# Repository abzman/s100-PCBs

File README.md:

# s100-PCBs
replica PCBs including backplanes and interface cards

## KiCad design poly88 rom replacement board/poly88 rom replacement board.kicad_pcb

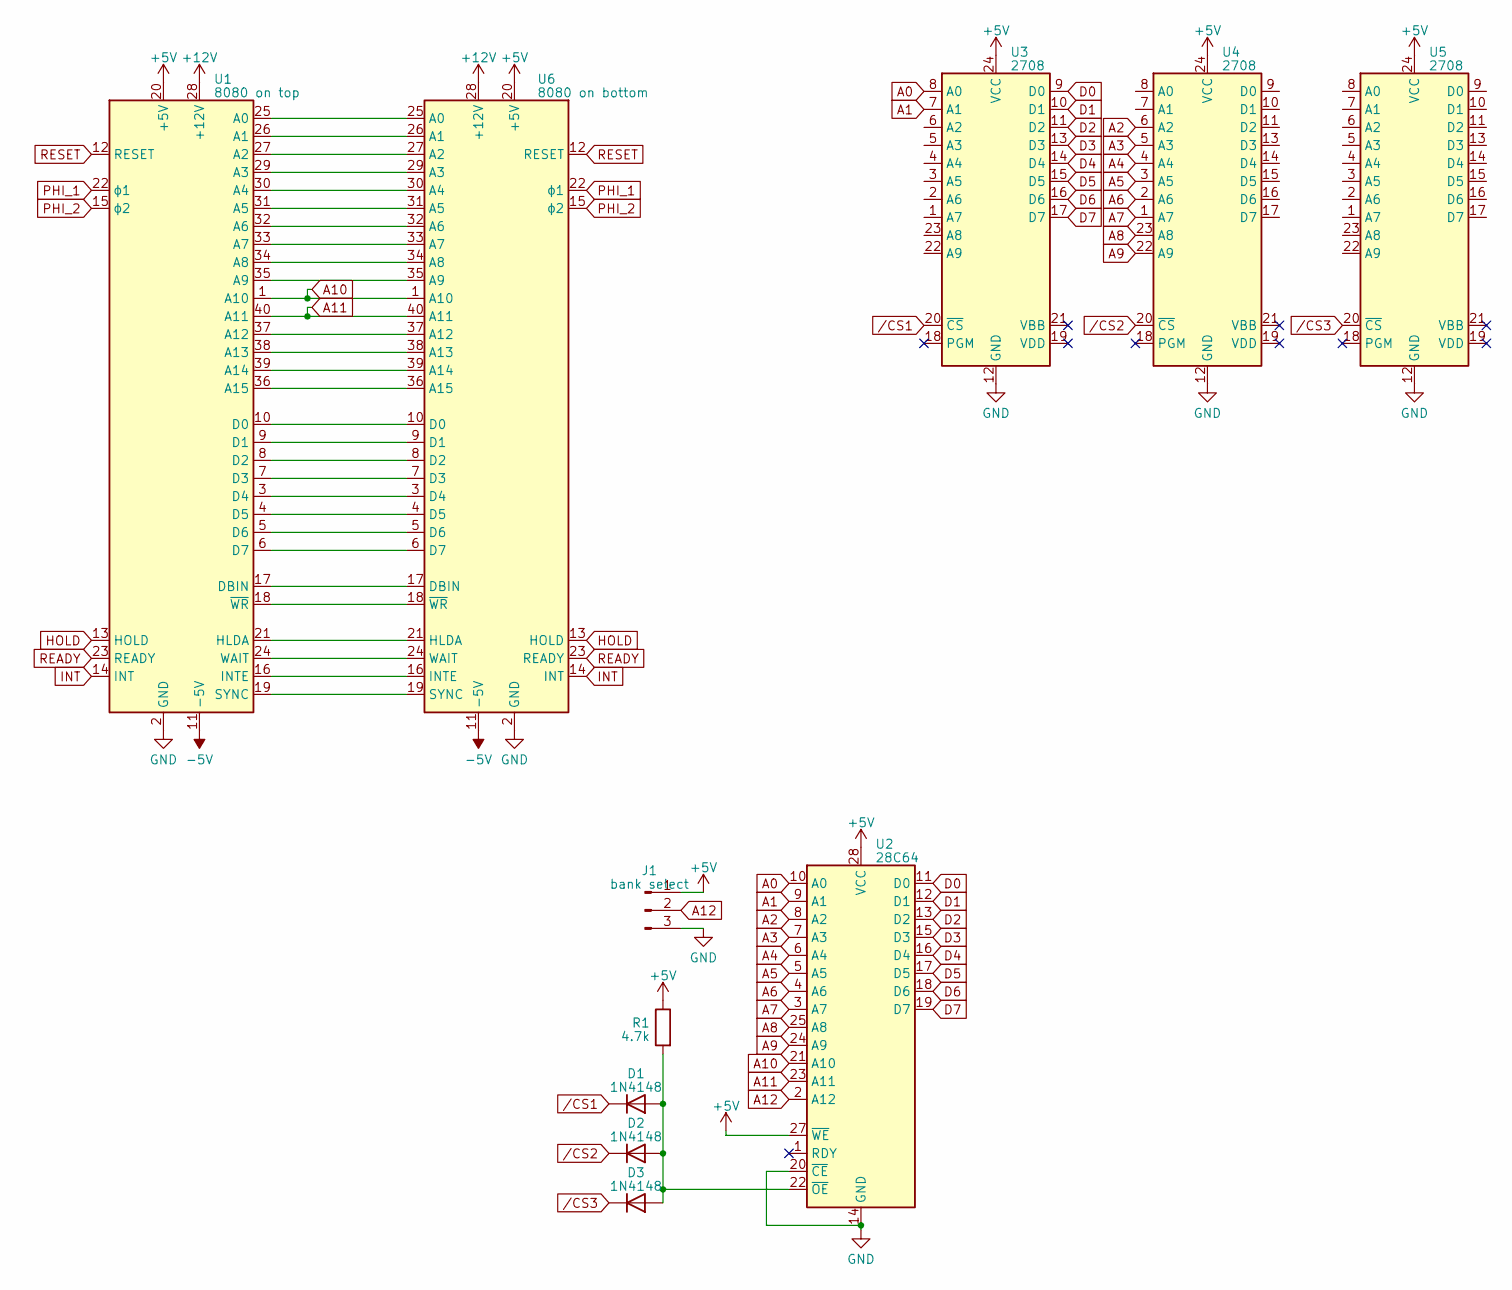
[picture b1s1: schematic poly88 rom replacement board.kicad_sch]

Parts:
D1, D2, D3: 1N4148; D_DO-35_SOD27_P7.62mm_Horizontal
J1: bank select; PinHeader_1x03_P2.54mm_Vertical
R1: 4.7k; R_Axial_DIN0207_L6.3mm_D2.5mm_P7.62mm_Horizontal
U1: 8080 on top; DIP-40_W15.24mm
U2: 28C64; DIP-28_W15.24mm
U3, U4, U5: 2708; DIP-24_W15.24mm
U6: 8080 on bottom; DIP-40_W15.24mm

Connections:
+5V: J1.1, R1.1, U1.20 (+5V), U2.27 (~WE), U2.28 (VCC), U3.24 (VCC), U4.24 (VCC), U5.24 (VCC), U6.20 (+5V)
+12V: U1.28 (+12V), U6.28 (+12V)
-5V: U1.11 (-5V), U6.11 (-5V)
A0: U2.10 (A0), U3.8 (A0)
A1: U2.9 (A1), U3.7 (A1)
A2: U2.8 (A2), U4.6 (A2)
A3: U2.7 (A3), U4.5 (A3)
A4: U2.6 (A4), U4.4 (A4)
A5: U2.5 (A5), U4.3 (A5)
A6: U2.4 (A6), U4.2 (A6)
A7: U2.3 (A7), U4.1 (A7)
A8: U2.25 (A8), U4.23 (A8)
A9: U2.24 (A9), U4.22 (A9)
A10: U1.1 (A10), U2.21 (A10), U6.1 (A10)
A11: U1.40 (A11), U2.23 (A11), U6.40 (A11)
A12: J1.2, U2.2 (A12)
D0: U2.11 (D0), U3.9 (D0)
D1: U2.12 (D1), U3.10 (D1)
D2: U2.13 (D2), U3.11 (D2)
D3: U2.15 (D3), U3.13 (D3)
D4: U2.16 (D4), U3.14 (D4)
D5: U2.17 (D5), U3.15 (D5)
D6: U2.18 (D6), U3.16 (D6)
D7: U2.19 (D7), U3.17 (D7)
GND: J1.3, U1.2 (GND), U2.14 (GND), U2.20 (~CE), U3.12 (GND), U4.12 (GND), U5.12 (GND), U6.2 (GND)
HOLD: U1.13 (HOLD), U6.13 (HOLD)
INT: U1.14 (INT), U6.14 (INT)
unnamed: D1.2 (A), D2.2 (A), D3.2 (A), R1.2, U2.22 (~OE)
unnamed: U1.25 (A0), U6.25 (A0)
unnamed: U1.26 (A1), U6.26 (A1)
unnamed: U1.27 (A2), U6.27 (A2)
unnamed: U1.29 (A3), U6.29 (A3)
unnamed: U1.30 (A4), U6.30 (A4)
unnamed: U1.31 (A5), U6.31 (A5)
unnamed: U1.32 (A6), U6.32 (A6)
unnamed: U1.33 (A7), U6.33 (A7)
unnamed: U1.34 (A8), U6.34 (A8)
unnamed: U1.35 (A9), U6.35 (A9)
unnamed: U1.37 (A12), U6.37 (A12)
unnamed: U1.38 (A13), U6.38 (A13)
unnamed: U1.39 (A14), U6.39 (A14)
unnamed: U1.36 (A15), U6.36 (A15)
unnamed: U1.10 (D0), U6.10 (D0)
unnamed: U1.9 (D1), U6.9 (D1)
unnamed: U1.8 (D2), U6.8 (D2)
unnamed: U1.7 (D3), U6.7 (D3)
unnamed: U1.3 (D4), U6.3 (D4)
unnamed: U1.4 (D5), U6.4 (D5)
unnamed: U1.5 (D6), U6.5 (D6)
unnamed: U1.6 (D7), U6.6 (D7)
unnamed: U1.17 (DBIN), U6.17 (DBIN)
unnamed: U1.21 (HLDA), U6.21 (HLDA)
unnamed: U1.16 (INTE), U6.16 (INTE)
unnamed: U1.19 (SYNC), U6.19 (SYNC)
unnamed: U1.24 (WAIT), U6.24 (WAIT)
unnamed: U1.18 (~WR), U6.18 (~WR)
PHI_1: U1.22 (ϕ1), U6.22 (ϕ1)
PHI_2: U1.15 (ϕ2), U6.15 (ϕ2)
READY: U1.23 (READY), U6.23 (READY)
RESET: U1.12 (RESET), U6.12 (RESET)
/CS1: D1.1 (K), U3.20 (~CS)
/CS2: D2.1 (K), U4.20 (~CS)
/CS3: D3.1 (K), U5.20 (~CS)

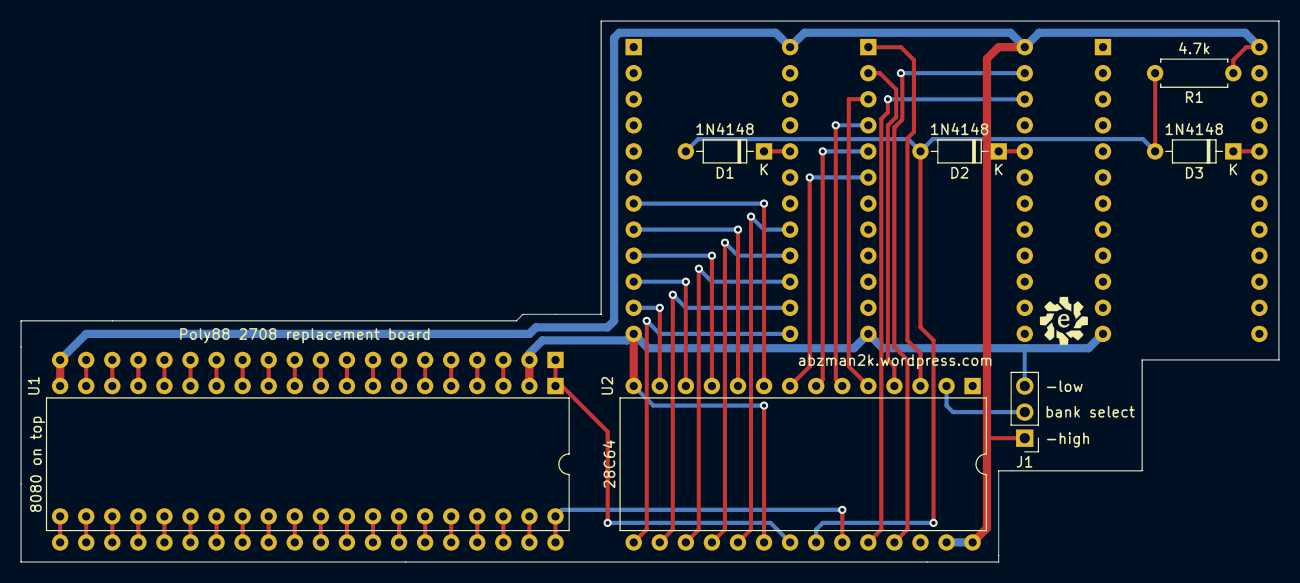
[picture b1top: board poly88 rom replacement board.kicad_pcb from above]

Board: 2 copper layers, 122.6 x 52.7 mm, 11 parts (0 on the bottom side), 63 nets.

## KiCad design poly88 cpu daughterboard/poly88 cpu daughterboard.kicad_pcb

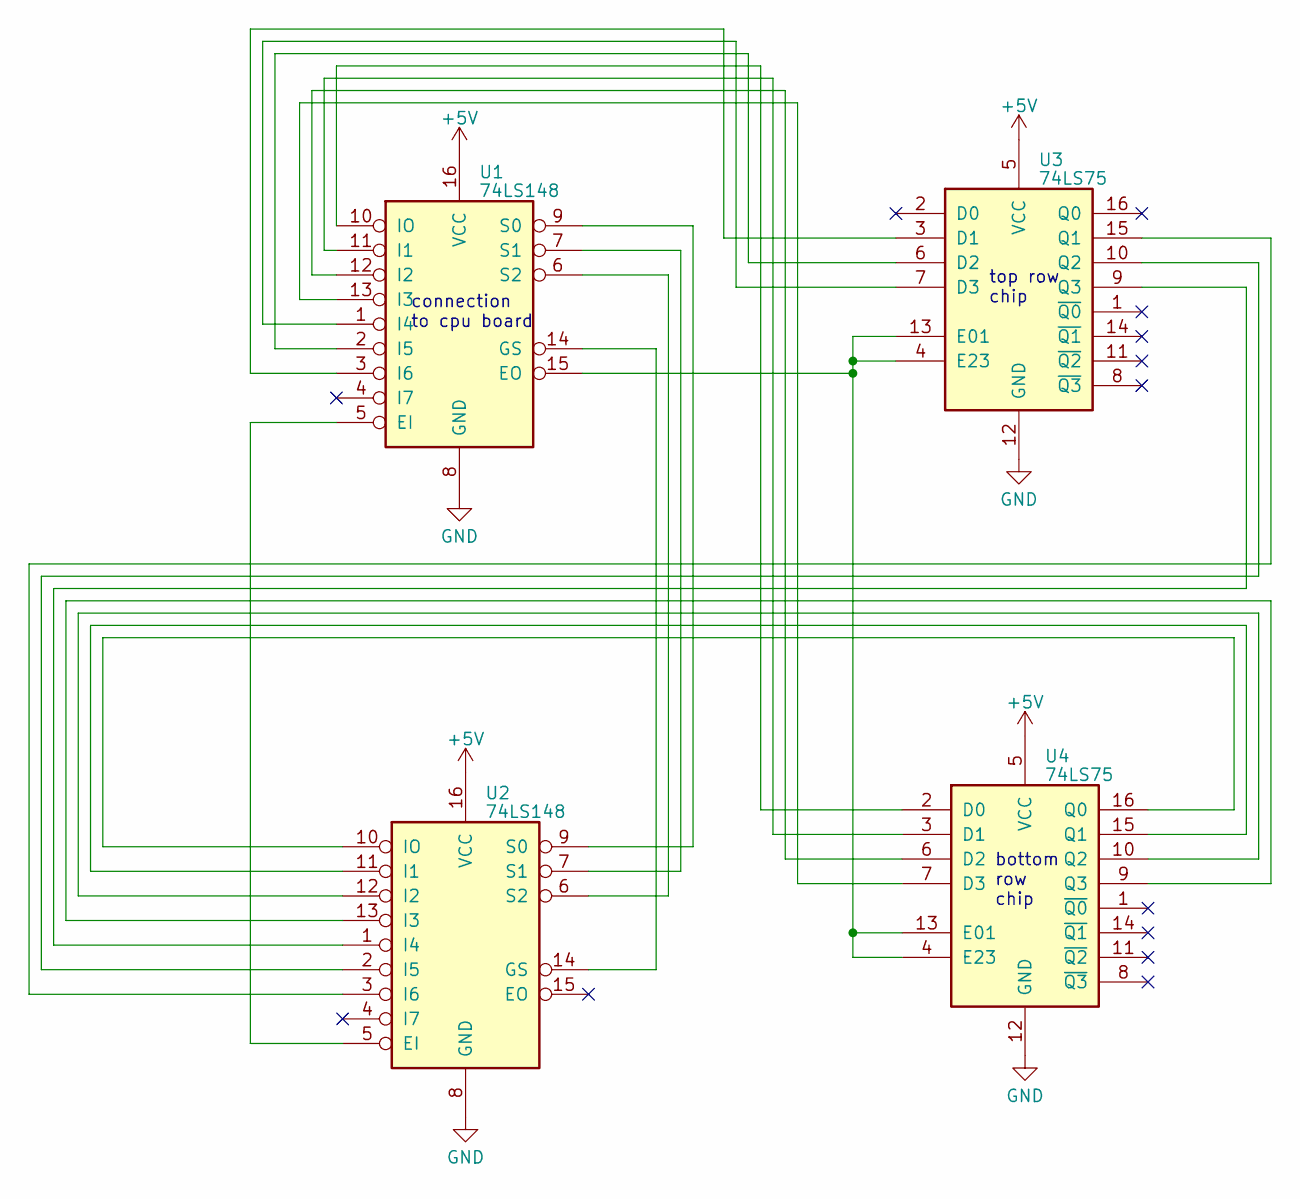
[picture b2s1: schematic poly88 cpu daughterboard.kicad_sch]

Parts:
U1, U2: 74LS148; DIP-16_W7.62mm
U3, U4: 74LS75; DIP-16_W7.62mm

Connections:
+5V: U1.16 (VCC), U2.16 (VCC), U3.5 (VCC), U4.5 (VCC)
GND: U1.8 (GND), U2.8 (GND), U3.12 (GND), U4.12 (GND)
unnamed: U1.5 (EI), U2.5 (EI)
unnamed: U1.15 (EO), U3.4 (E23), U3.13 (E01), U4.4 (E23), U4.13 (E01)
unnamed: U1.14 (GS), U2.14 (GS)
unnamed: U1.11 (I1), U4.3 (D1)
unnamed: U1.12 (I2), U4.6 (D2)
unnamed: U1.13 (I3), U4.7 (D3)
unnamed: U1.1 (I4), U3.7 (D3)
unnamed: U1.2 (I5), U3.6 (D2)
unnamed: U1.3 (I6), U3.3 (D1)
unnamed: U1.10 (IO), U4.2 (D0)
unnamed: U1.9 (S0), U2.9 (S0)
unnamed: U1.7 (S1), U2.7 (S1)
unnamed: U1.6 (S2), U2.6 (S2)
unnamed: U2.11 (I1), U4.15 (Q1)
unnamed: U2.12 (I2), U4.10 (Q2)
unnamed: U2.13 (I3), U4.9 (Q3)
unnamed: U2.1 (I4), U3.9 (Q3)
unnamed: U2.2 (I5), U3.10 (Q2)
unnamed: U2.3 (I6), U3.15 (Q1)
unnamed: U2.10 (IO), U4.16 (Q0)

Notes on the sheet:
top row chip
bottom row chip
connection to cpu board

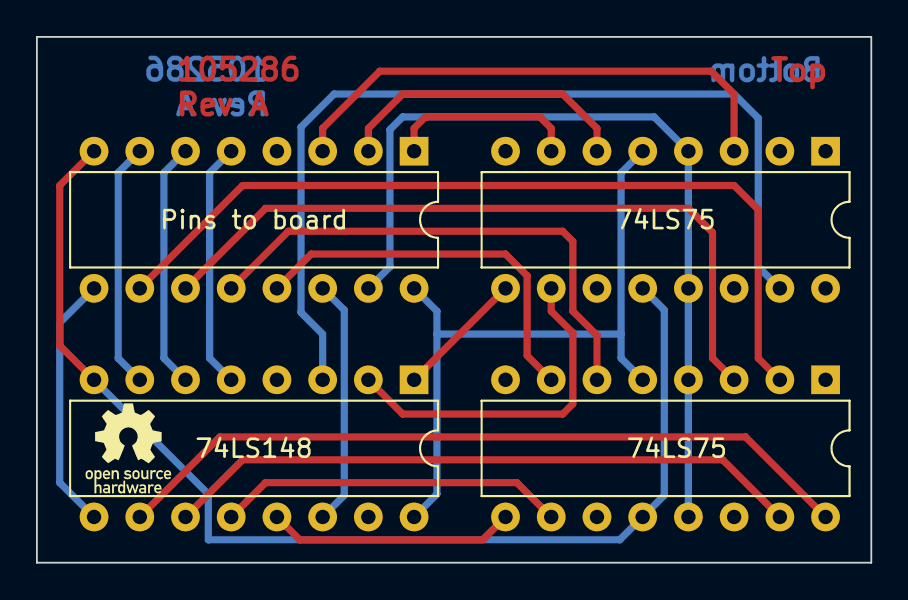
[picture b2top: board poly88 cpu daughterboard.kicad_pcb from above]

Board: 2 copper layers, 46.4 x 29.2 mm, 4 parts (0 on the bottom side), 22 nets.

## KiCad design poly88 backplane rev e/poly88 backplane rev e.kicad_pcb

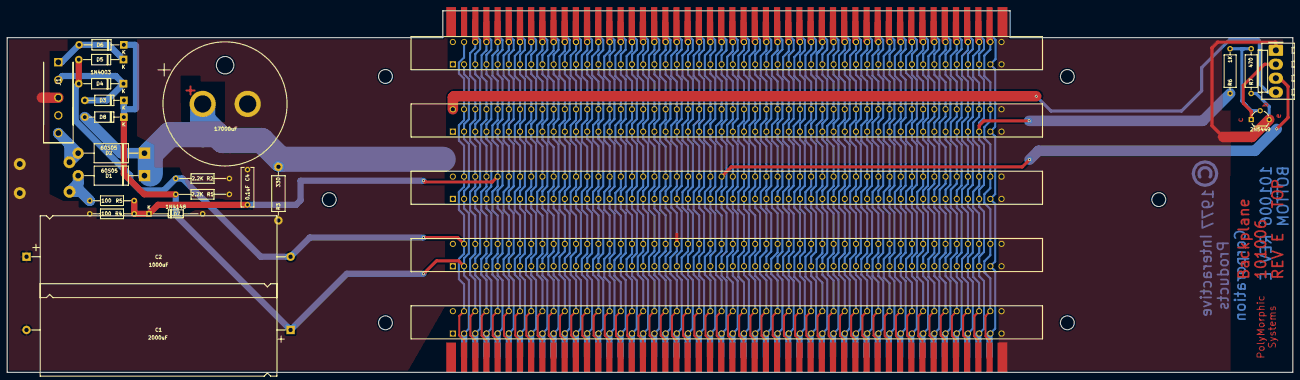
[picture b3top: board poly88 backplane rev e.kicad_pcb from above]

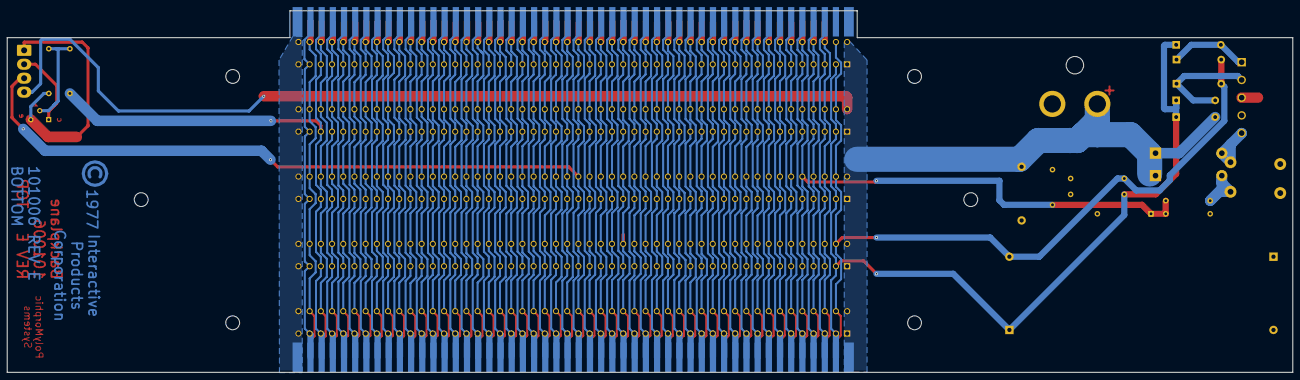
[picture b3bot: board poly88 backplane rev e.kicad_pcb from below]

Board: 2 copper layers, 365.1 x 102.7 mm, 33 parts (2 on the bottom side), 103 nets.

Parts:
C1: 2000uF; CP_Axial_L67.0mm_D26.0mm_P75.00mm_Horizontal
C2: 1000uF; CP_Axial_L67.0mm_D23.0mm_P75.00mm_Horizontal
C3: 17000uF; CP_Radial_D35.0mm_P12.90mm_SnapIn
C4: 0.1uF; C_Rect_L11.0mm_W3.4mm_P10.00mm_MKT
D1, D2: 60S05; D_DO-201AD_P18.83mm_Horizontal
D3, D4, D5, D6, D8: 1N4003; D_DO-41_SOD81_P12.70mm_Horizontal
D7: 1N4148; D_DO-35_SOD27_P15.24mm_Horizontal
J1: Power In; 5 pin inline molex 0.93
J2: Switch and Light; Molex_KK-396_A-41791-0004_1x04_P3.96mm_Vertical
J3, J11, J12, J13: Conn_01x01; Pin_D1.0mm_L10.0mm
J4: Card Edge in; BUS_S100_M
J5, J6, J7, J8, J9: 346-100-520-802; 346100520802
J10: edge mount connector; BUS_S100_M
Q1: 2N5449; TO-92_Wide
R1, R2: 2.2K; R_Axial_DIN0207_L6.3mm_D2.5mm_P15.24mm_Horizontal
R3: 330; R_Axial_DIN0411_L9.9mm_D3.6mm_P15.24mm_Horizontal
R4, R5: 100; R_Axial_DIN0207_L6.3mm_D2.5mm_P10.16mm_Horizontal
R6: 1K; R_Axial_DIN0309_L9.0mm_D3.2mm_P12.70mm_Horizontal
R7: 470; R_Axial_DIN0309_L9.0mm_D3.2mm_P12.70mm_Horizontal

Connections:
1: C3.1, D1.1 (K), D2.1 (K), D8.2 (A), J2.4, J4.1, J4.51, J5.1, J5.51, J6.1, J6.51, J7.1, J7.51, J8.1, J8.51, J9.1, J9.51, R3.1
2: C1.1, D3.1 (K), D6.1 (K), D8.1 (K), J4.2, J5.2, J6.2, J7.2, J8.2, J9.2, R1.1
3: J4.3, J5.3, J6.3, J7.3, J8.3, J9.3, J10.3
4: J4.4, J5.4, J6.4, J7.4, J8.4, J9.4, J10.4
5: J4.5, J5.5, J6.5, J7.5, J8.5, J9.5, J10.5
6: J4.6, J5.6, J6.6, J7.6, J8.6, J9.6, J10.6
7: J4.7, J5.7, J6.7, J7.7, J8.7, J9.7, J10.7
8: J4.8, J5.8, J6.8, J7.8, J8.8, J9.8, J10.8
9: J4.9, J5.9, J6.9, J7.9, J8.9, J9.9, J10.9
10: J4.10, J5.10, J6.10, J7.10, J8.10, J9.10, J10.10
11: J4.11, J5.11, J6.11, J7.11, J8.11, J9.11, J10.11
12: J4.12, J5.12, J6.12, J7.12, J8.12, J9.12, J10.12
13: J4.13, J5.13, J6.13, J7.13, J8.13, J9.13, J10.13
14: J4.14, J5.14, J6.14, J7.14, J8.14, J9.14, J10.14
15: J4.15, J5.15, J6.15, J7.15, J8.15, J9.15, J10.15
16: J4.16, J5.16, J6.16, J7.16, J8.16, J9.16, J10.16
17: J4.17, J5.17, J6.17, J7.17, J8.17, J9.17, J10.17
18: J4.18, J5.18, J6.18, J7.18, J8.18, J9.18, J10.18
19: J4.19, J5.19, J6.19, J7.19, J8.19, J9.19, J10.19
20: J4.20, J5.20, J6.20, J7.20, J8.20, J9.20, J10.20
21: J4.21, J5.21, J6.21, J7.21, J8.21, J9.21, J10.21
22: J4.22, J5.22, J6.22, J7.22, J8.22, J9.22, J10.22
23: J4.23, J5.23, J6.23, J7.23, J8.23, J9.23, J10.23
24: J4.24, J5.24, J6.24, J7.24, J8.24, J9.24, J10.24
25: J4.25, J5.25, J6.25, J7.25, J8.25, J9.25, J10.25
26: J4.26, J5.26, J6.26, J7.26, J8.26, J9.26, J10.26
27: J4.27, J5.27, J6.27, J7.27, J8.27, J9.27, J10.27
28: J4.28, J5.28, J6.28, J7.28, J8.28, J9.28, J10.28
29: J4.29, J5.29, J6.29, J7.29, J8.29, J9.29, J10.29
30: J4.30, J5.30, J6.30, J7.30, J8.30, J9.30, J10.30
31: J4.31, J5.31, J6.31, J7.31, J8.31, J9.31, J10.31
32: J4.32, J5.32, J6.32, J7.32, J8.32, J9.32, J10.32
33: J4.33, J5.33, J6.33, J7.33, J8.33, J9.33, J10.33
34: J4.34, J5.34, J6.34, J7.34, J8.34, J9.34, J10.34
35: J4.35, J5.35, J6.35, J7.35, J8.35, J9.35, J10.35
36: J4.36, J5.36, J6.36, J7.36, J8.36, J9.36, J10.36
37: J4.37, J5.37, J6.37, J7.37, J8.37, J9.37, J10.37
38: J4.38, J5.38, J6.38, J7.38, J8.38, J9.38, J10.38
39: J4.39, J5.39, J6.39, J7.39, J8.39, J9.39, J10.39
40: J4.40, J5.40, J6.40, J7.40, J8.40, J9.40, J10.40
41: J4.41, J5.41, J6.41, J7.41, J8.41, J9.41, J10.41
42: J4.42, J5.42, J6.42, J7.42, J8.42, J9.42, J10.42
43: J4.43, J5.43, J6.43, J7.43, J8.43, J9.43, J10.43
44: J4.44, J5.44, J6.44, J7.44, J8.44, J9.44, J10.44
45: J4.45, J5.45, J6.45, J7.45, J8.45, J9.45, J10.45
46: J4.46, J5.46, J6.46, J7.46, J8.46, J9.46, J10.46
47: J4.47, J5.47, J6.47, J7.47, J8.47, J9.47, J10.47
48: J4.48, J5.48, J6.48, J7.48, J8.48, J9.48, J10.48, R6.2
49: J4.49, J5.49, J6.49, J7.49, J8.49, J9.49, J10.49
52: C2.2, D4.2 (A), D5.2 (A), J4.52, J5.52, J6.52, J7.52, J8.52, J9.52, R2.1
53: J4.53, J5.53, J6.53, J7.53, J8.53, J9.53, J10.53
54: J4.54, J5.54, J6.54, J7.54, J8.54, J9.54, J10.54
55: C4.1, D7.1 (K), J4.55, J5.55, J6.55, J7.55, J8.55, J9.55, J10.55, R4.1, R5.1
56: J4.56, J5.56, J6.56, J7.56, J8.56, J9.56, J10.56
57: J4.57, J5.57, J6.57, J7.57, J8.57, J9.57, J10.57
58: J4.58, J5.58, J6.58, J7.58, J8.58, J9.58, J10.58
59: J4.59, J5.59, J6.59, J7.59, J8.59, J9.59, J10.59
60: J4.60, J5.60, J6.60, J7.60, J8.60, J9.60, J10.60
61: J4.61, J5.61, J6.61, J7.61, J8.61, J9.61, J10.61
62: J4.62, J5.62, J6.62, J7.62, J8.62, J9.62, J10.62
63: J4.63, J5.63, J6.63, J7.63, J8.63, J9.63, J10.63
64: J4.64, J5.64, J6.64, J7.64, J8.64, J9.64, J10.64
65: J4.65, J5.65, J6.65, J7.65, J8.65, J9.65, J10.65
66: J4.66, J5.66, J6.66, J7.66, J8.66, J9.66, J10.66
67: J4.67, J5.67, J6.67, J7.67, J8.67, J9.67, J10.67
68: J4.68, J5.68, J6.68, J7.68, J8.68, J9.68, J10.68
69: J4.69, J5.69, J6.69, J7.69, J8.69, J9.69, J10.69
70: J4.70, J5.70, J6.70, J7.70, J8.70, J9.70, J10.70
72: J4.72, J5.72, J6.72, J7.72, J8.72, J9.72, J10.72
73: J4.73, J5.73, J6.73, J7.73, J8.73, J9.73, J10.73
74: J4.74, J5.74, J6.74, J7.74, J8.74, J9.74, J10.74
75: J2.3, J4.75, J5.75, J6.75, J7.75, J8.75, J9.75, J10.75
76: J4.76, J5.76, J6.76, J7.76, J8.76, J9.76, J10.76
77: J4.77, J5.77, J6.77, J7.77, J8.77, J9.77, J10.77
78: J4.78, J5.78, J6.78, J7.78, J8.78, J9.78, J10.78
79: J4.79, J5.79, J6.79, J7.79, J8.79, J9.79, J10.79
80: J4.80, J5.80, J6.80, J7.80, J8.80, J9.80, J10.80
81: J4.81, J5.81, J6.81, J7.81, J8.81, J9.81, J10.81
82: J4.82, J5.82, J6.82, J7.82, J8.82, J9.82, J10.82
83: J4.83, J5.83, J6.83, J7.83, J8.83, J9.83, J10.83
84: J4.84, J5.84, J6.84, J7.84, J8.84, J9.84, J10.84
85: J4.85, J5.85, J6.85, J7.85, J8.85, J9.85, J10.85
86: J4.86, J5.86, J6.86, J7.86, J8.86, J9.86, J10.86
87: J4.87, J5.87, J6.87, J7.87, J8.87, J9.87, J10.87
88: J4.88, J5.88, J6.88, J7.88, J8.88, J9.88, J10.88
89: J4.89, J5.89, J6.89, J7.89, J8.89, J9.89, J10.89
90: J4.90, J5.90, J6.90, J7.90, J8.90, J9.90, J10.90
91: J4.91, J5.91, J6.91, J7.91, J8.91, J9.91, J10.91
92: J4.92, J5.92, J6.92, J7.92, J8.92, J9.92, J10.92
93: J4.93, J5.93, J6.93, J7.93, J8.93, J9.93, J10.93
94: J4.94, J5.94, J6.94, J7.94, J8.94, J9.94, J10.94
95: J4.95, J5.95, J6.95, J7.95, J8.95, J9.95, J10.95
96: J4.96, J5.96, J6.96, J7.96, J8.96, J9.96, J10.96
97: J4.97, J5.97, J6.97, J7.97, J8.97, J9.97, J10.97
98: J4.98, J5.98, J6.98, J7.98, J8.98, J9.98, J10.98
99: J4.99, J5.99, J6.99, J7.99, J8.99, J9.99, J10.99
100: C1.2, C2.1, C3.2, C4.2, D7.2 (A), J1.3, J2.1, J4.50, J4.71, J4.100, J5.50, J5.71, J5.100, J6.50, J6.71, J6.100, J7.50, J7.71, J7.100, J8.50, J8.71, J8.100, J9.50, J9.71, J9.100, J10.50, J10.71, J10.100, J12.1, J13.1, Q1.3 (E), R1.2, R2.2, R3.2, R4.2, R7.2
unnamed: D5.1 (K), D6.2 (A), J1.1
unnamed: D1.2 (A), J1.4, J11.1, R5.2
unnamed: D2.2 (A), J1.5, J3.1
unnamed: D3.2 (A), D4.1 (K), J1.2
unnamed: J2.2, Q1.1 (C)
unnamed: Q1.2 (B), R6.1, R7.1

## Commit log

2022-10-25 schematic and footprints done, probably
2022-10-27 components placed
2022-10-27 both layouts done?
2022-11-09 finished rev 2.1 pcb with annotations
2022-11-25 generated gerbers
2023-08-28 added little undocumented daughterboard from poly88 cpu board
2023-12-13 added new boards, VTI and poly88 cpu interposer board
2025-09-02 updated to kicad 9
2025-09-02 added scans of rev. F
2025-09-02 added photos of rev f disassembly
2025-09-02 added photos during disassembly and testing of some boards
2025-09-06 added new variant of vti parallel interface
2025-09-12 updating poly stuff
2025-11-06 added newtech computers sound card pictures
2026-04-22 removed irrelevant pics
